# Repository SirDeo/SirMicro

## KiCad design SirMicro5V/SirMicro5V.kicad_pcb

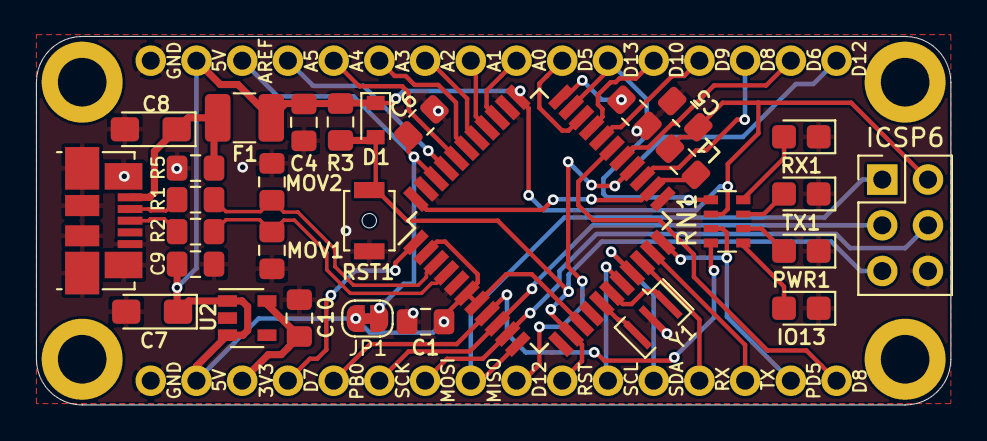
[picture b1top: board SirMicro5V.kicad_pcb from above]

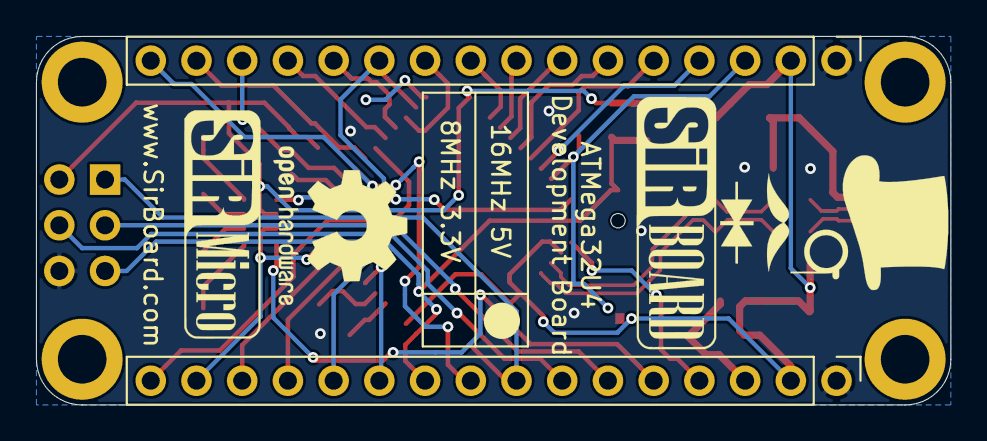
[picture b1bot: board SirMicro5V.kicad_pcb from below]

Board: 2 copper layers, 50.8 x 20.5 mm, 32 parts (2 on the bottom side), 42 nets.

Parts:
C1, C9, C10: 1uF; C_0805_2012Metric_Pad1.15x1.40mm_HandSolder
C4, C5, C6: 100nF; C_0805_2012Metric_Pad1.15x1.40mm_HandSolder
C7: 1uF; CP_EIA-3216-18_Kemet-A_Pad1.58x1.35mm_HandSolder
C8: 22uF; CP_EIA-3216-18_Kemet-A_Pad1.58x1.35mm_HandSolder
D1: D; D_SOD-110
F1: 500mA; R_1210_3225Metric_Pad1.42x2.65mm_HandSolder
ICSP6: Conn_02x03_Odd_Even; PinHeader_2x03_P2.54mm_Vertical
IO13: LED; LED_0805_2012Metric_Castellated
J1, J2: Conn_01x16; PinHeader_1x16_P2.54mm_Vertical
J3: USB_B_Micro; USB_Micro-B_Molex_47346-0001
JP1: SolderJumper_2_Bridged; SolderJumper-2_P1.3mm_Bridged_RoundedPad1.0x1.5mm
L1: 10uH; L_0805_2012Metric_Pad1.15x1.40mm_HandSolder
MOV1, MOV2: 5V; R_0805_2012Metric_Pad1.15x1.40mm_HandSolder
PWR1: LED; LED_0805_2012Metric_Castellated
R1, R2, R4: 22e; R_0805_2012Metric_Pad1.15x1.40mm_HandSolder
R3, R5: 10k; R_0805_2012Metric_Pad1.15x1.40mm_HandSolder
RN1: 1k; R_Array_Convex_4x0603
RST1: SW_Push; SW_SPST_B3U-1000P-B
RX1: LED; LED_0805_2012Metric_Castellated
TX1: LED; LED_0805_2012Metric_Castellated
U1: ATmega32U4-AU; TQFP-44_10x10mm_P0.8mm
U2: AP2127K-3.3; SOT-23-5
Y1: Resonator; Resonator_SMD_muRata_CSTxExxV-3Pin_3.0x1.1mm

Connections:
3V3: C10.1, J2.3, U2.5
5V: C1.1, C4.1, C5.1, C7.1, C9.1, D1.1, F1.1, ICSP6.2, J1.2, J2.2, JP1.1, L1.1, R3.1, RN1.2, U1.2, U1.6, U1.7, U1.14, U1.34, U2.1, U2.3
/D+: J3.3, R2.1
/D-: J3.2, R1.1
/HWB: R4.1, U1.33
/Vbus: C8.1, F1.2, J3.1, R5.1
/X1: U1.17, Y1.1
/X2: U1.16, Y1.3
/uD+: MOV1.1, R2.2, U1.4
/uD-: MOV2.1, R1.2, U1.3
A0: J1.9, U1.36
A1: J1.8, U1.37
A2: J1.7, U1.38
A3: J1.6, U1.39
A4: J1.5, U1.40
A5: J1.4, U1.41
AREF: C6.1, J1.3, JP1.2, U1.42
D4: J1.14, U1.25
D5: J1.10, U1.31
D6: J1.15, U1.27
D7: J2.4, U1.1
D8: J2.16, U1.28
D9: J1.13, U1.29
D10: J1.12, U1.30
D12: J1.16, J2.9, U1.26
D13: J1.11, RN1.1, U1.32
GND: C1.2, C4.2, C5.2, C6.2, C7.2, C8.2, C9.2, C10.2, ICSP6.6, IO13.1, J1.1, J2.1, J3.5, J3.6, MOV1.2, MOV2.2, PWR1.1, R4.2, R5.2, RST1.1, RX1.1, TX1.1, U1.5, U1.15, U1.23, U1.35, U1.43, U2.2, Y1.2
MISO: ICSP6.1, J2.8, U1.11
MOSI: ICSP6.4, J2.7, U1.10
unnamed: IO13.2, RN1.5
unnamed: L1.2, U1.24, U1.44
unnamed: PWR1.2, RN1.6
unnamed: RN1.7, TX1.2
unnamed: RN1.8, RX1.2
RST: D1.2, ICSP6.5, J2.10, R3.2, RST1.2, U1.13
RX: J2.13, U1.20
RXLED: J2.5, RN1.4, U1.8
SCK: ICSP6.3, J2.6, U1.9
SCL: J2.11, U1.18
SDA: J2.12, U1.19
TX: J2.14, U1.21
TXLED: J2.15, RN1.3, U1.22

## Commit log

2019-07-20 Initial Commit of 5V variant
2019-07-20 PCB Silkscreen revised
2019-07-20 Board Layout revised and 3V3 Version Added
2019-07-20 Jumper Edited
2019-07-27 Dual Voltage And Voltage Selector Added, QFN Package used
2019-07-28 Jumpers Moved
2019-08-06 Dimensions Updated
2019-08-20 Layout updated and silkscreen revised
2019-08-21 LDO changed
2019-09-09 Regulator changed from AP to AZ
2019-09-19 Capacitor Footprint change
    3216 to 3512
2019-12-04 Part Numbers Added
2019-12-21 SirMicro5V and SirMicro3V3 Removed
2020-01-08 Schematic PDF and 3D Renders added
2020-03-05 SirMicro Version 3 Added
    USB-C, Dual MCP4725 DACs, SirBlue (Qwiic, Stemma QT) Connector, Arduino Micro Form Factor + Pinout
2020-03-12 Soldermask width adjusted
2020-03-19 Schematic Update - SirMicroR3
    20Mhz Changed to 16Mhz
2020-03-19 SirMicroR3 Update
    Silkscreen Edits
2020-04-11 SirMicro Update
    USB-C 3D Renders Added and Pictures Updated
